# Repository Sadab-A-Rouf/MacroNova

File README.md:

<h1>MacroNova</h1>
<p>So, I decided to build a 4x4 macro pad for Hack Club Macondo, and MacroNova is 
basically my take on a clean, fully programmable desktop controller. The whole goal 
here is to cram 16 mechanical switches, an OLED screen, and a bunch of custom 
shortcuts into a compact, handwired build that makes workflow a lot faster.</p>

<h2>How It Works</h2>
<p>Instead of doing a lazy wiring job and wasting 16 separate GPIO pins on the 
microcontroller, I am wiring the switches into a <strong>4x4 matrix</strong>. This 
drops the required pins down to just 8. To make sure the board doesn't register fake 
keypresses when I smash multiple buttons at once, I am adding a 1N4148 diode to every 
single switch to block ghosting entirely.</p>

<p>The brain of the project is an <strong>ESP32-C3-DevKitM-1</strong>. Connected to 
that is an ER-OLEDM0.91 display running over I2C, which will give me live visual 
feedback on whatever layer or profile is currently active. Two 4.7kΩ pull-up resistors 
sit on the SCL and SDA lines to keep I2C communication stable and reliable. For the 
software side, I am flashing CircuitPython and using the KMK firmware framework because 
it makes updating macros and remapping keys on the fly incredibly easy.</p>

<h2>Current Status</h2>
<p>Schematic is fully complete. The 4x4 key matrix, diode placement, OLED wiring, I2C 
pull-up resistors, and all ESP32-C3 pinouts are finalized and verified. The bill of 
materials is ready for Macondo reviewers. Waiting on funding approval — once parts 
arrive, build and soldering logs go right here.</p>

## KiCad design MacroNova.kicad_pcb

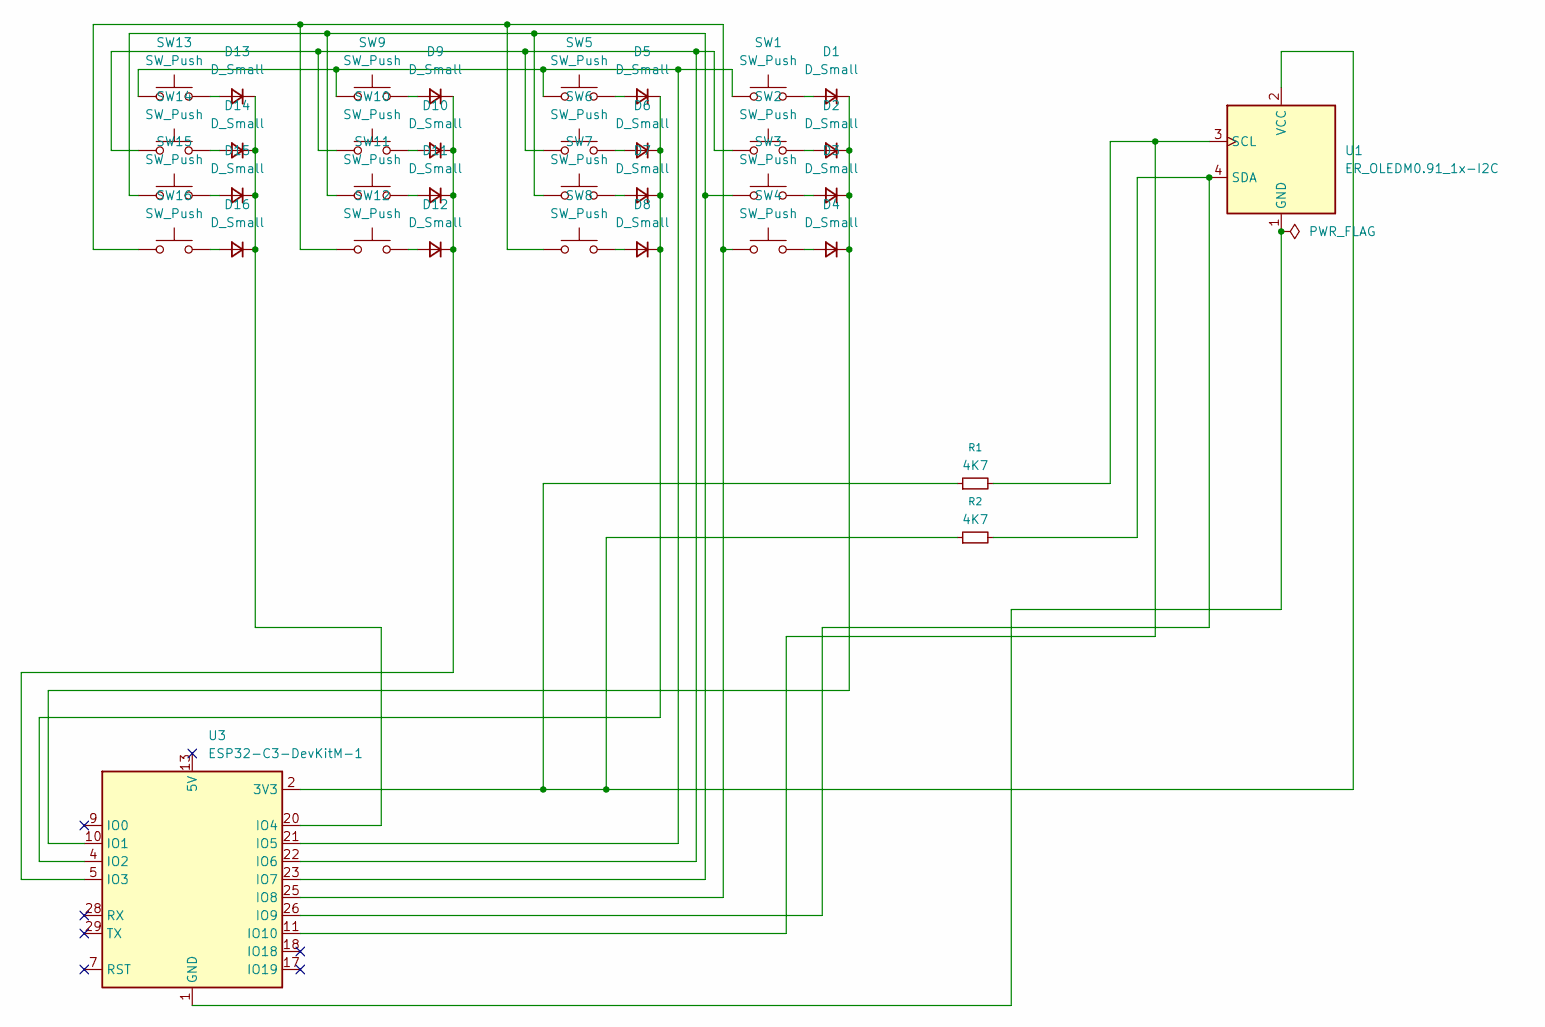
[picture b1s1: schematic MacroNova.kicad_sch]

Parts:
D1, D2, D3, D4, D5, D6, D7, D8, D9, D10, D11, D12, D13, D14, D15, D16: D_Small; D_DO-35_SOD27_P7.62mm_Horizontal
R1, R2: 4K7; R_Axial_DIN0207_L6.3mm_D2.5mm_P10.16mm_Horizontal
SW1, SW2, SW3, SW4, SW5, SW6, SW7, SW8, SW9, SW10, SW11, SW12, SW13, SW14, SW15, SW16: SW_Push; SW_Cherry_MX_1.00u_PCB
U1: ER_OLEDM0.91_1x-I2C; PinHeader_1x04_P2.54mm_Vertical
U3: ESP32-C3-DevKitM-1

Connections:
unnamed: D1.2 (A), SW1.2
unnamed: D1.1 (K), D2.1 (K), D3.1 (K), D4.1 (K), U3.10 (IO1)
unnamed: D2.2 (A), SW2.2
unnamed: D3.2 (A), SW3.2
unnamed: D4.2 (A), SW4.2
unnamed: D5.2 (A), SW5.2
unnamed: D5.1 (K), D6.1 (K), D7.1 (K), D8.1 (K), U3.4 (IO2)
unnamed: D6.2 (A), SW6.2
unnamed: D7.2 (A), SW7.2
unnamed: D8.2 (A), SW8.2
unnamed: D9.2 (A), SW9.2
unnamed: D10.2 (A), SW10.2
unnamed: D9.1 (K), D10.1 (K), D11.1 (K), D12.1 (K), U3.5 (IO3)
unnamed: D11.2 (A), SW11.2
unnamed: D12.2 (A), SW12.2
unnamed: D13.2 (A), SW13.2
unnamed: D13.1 (K), D14.1 (K), D15.1 (K), D16.1 (K), U3.20 (IO4)
unnamed: D14.2 (A), SW14.2
unnamed: D15.2 (A), SW15.2
unnamed: D16.2 (A), SW16.2
unnamed: U1.1 (GND), U3.1 (GND), U3.6 (GND), U3.8 (GND), U3.12 (GND), U3.15 (GND), U3.16 (GND), U3.19 (GND), U3.24 (GND), U3.27 (GND), U3.30 (GND)
unnamed: R1.2, U1.3 (SCL), U3.11 (IO10)
unnamed: R2.2, U1.4 (SDA), U3.26 (IO9)
unnamed: R1.1, R2.1, U1.2 (VCC), U3.2 (3V3), U3.3 (3V3)
unnamed: SW1.1, SW5.1, SW9.1, SW13.1, U3.21 (IO5)
unnamed: SW2.1, SW6.1, SW10.1, SW14.1, U3.22 (IO6)
unnamed: SW3.1, SW7.1, SW11.1, SW15.1, U3.23 (IO7)
unnamed: SW4.1, SW8.1, SW12.1, SW16.1, U3.25 (IO8)

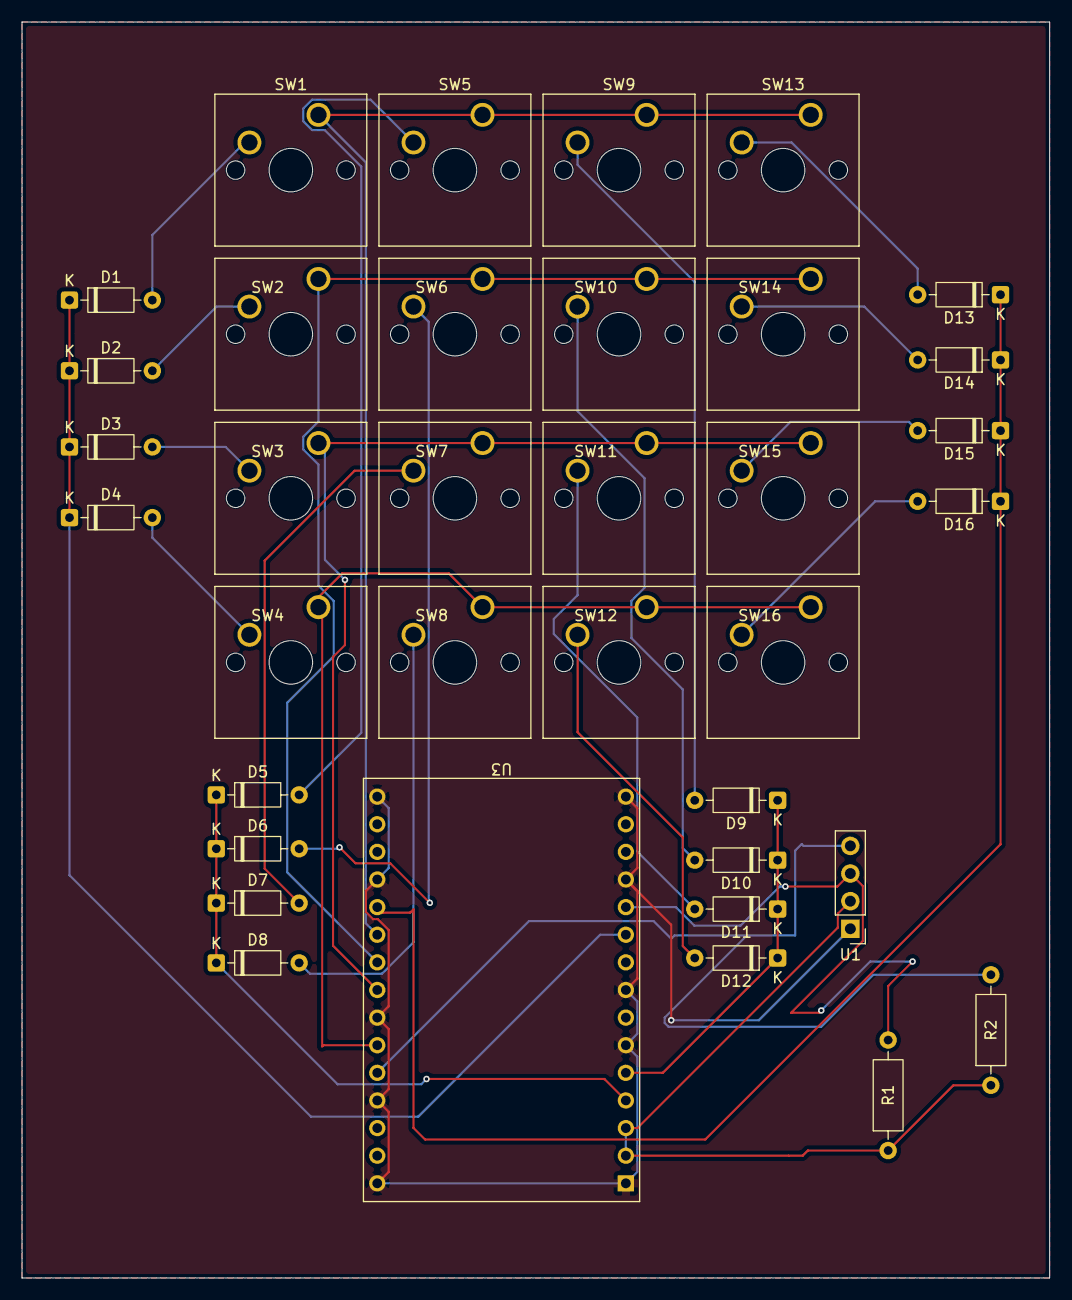
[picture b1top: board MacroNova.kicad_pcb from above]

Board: 2 copper layers, 94.5 x 115.5 mm, 36 parts (0 on the bottom side), 28 nets.

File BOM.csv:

"Reference","Qty","Value","DNP","Exclude from BOM","Exclude from Board","Footprint","Datasheet"
"D1,D2,D3,D4,D5,D6,D7,D8,D9,D10,D11,D12,D13,D14,D15,D16","16","D_Small","","","","Diode_THT:D_DO-35_SOD27_P7.62mm_Horizontal",""
"R1,R2","2","4K7","","","","Resistor_THT:R_Axial_DIN0207_L6.3mm_D2.5mm_P10.16mm_Horizontal",""
"SW1,SW2,SW3,SW4,SW5,SW6,SW7,SW8,SW9,SW10,SW11,SW12,SW13,SW14,SW15,SW16","16","SW_Push","","","","Button_Switch_Keyboard:SW_Cherry_MX_1.00u_PCB",""
"U1","1","ER_OLEDM0.91_1x-I2C","","","","Connector_PinHeader_2.54mm:PinHeader_1x04_P2.54mm_Vertical","https://www.buydisplay.com/download/manual/ER-OLEDM0.91-1_Da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"
"U3","1","ESP32-C3-DevKitM-1","","","","RF_Module:ESP32-C3-DevKitM-1","https://docs.espressif.com/projects/esp-idf/en/latest/esp32c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"

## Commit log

2026-06-14 Revise README with project details and status
    Expanded project description and added details on functionality and current status.
2026-06-16 Revise README with updated project information
    Updated project details including hardware specifications and current status.
2026-06-16 Add schematic images to README
    Added multiple schematic images to the README.
2026-06-16 Rename MacroNova.csv to BOM.csv
2026-06-16 Revise BOM format and include purchase links
    Updated the Bill of Materials format and added purchase links for components.
2026-06-17 Replace PNG with SVG for matrix diagram in README
